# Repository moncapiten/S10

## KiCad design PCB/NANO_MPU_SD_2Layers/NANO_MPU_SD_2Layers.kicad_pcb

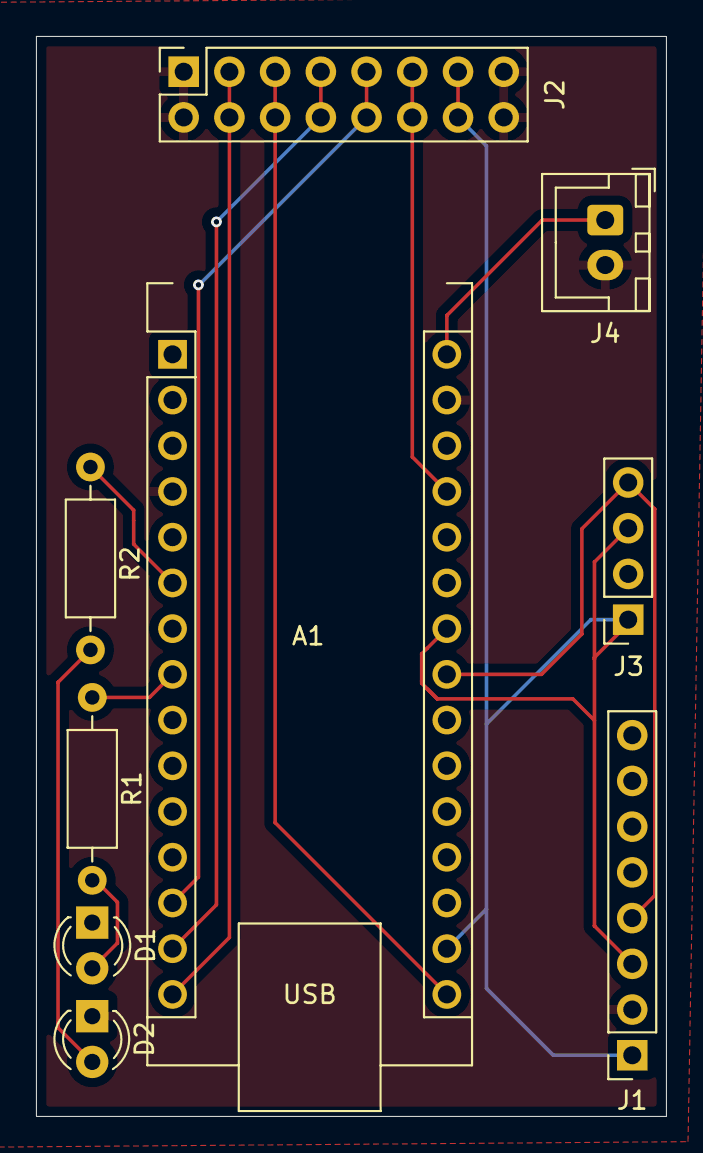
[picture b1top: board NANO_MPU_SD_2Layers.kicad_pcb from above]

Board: 2 copper layers, 35.0 x 60.0 mm, 9 parts (0 on the bottom side), 14 nets.

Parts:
A1: Arduino_Nano_v2.x; Arduino_Nano
D1, D2: LED; LED_D3.0mm_Clear
J1: Conn_01x08_Socket; PinSocket_1x08_P2.54mm_Vertical
J2: DIN41612_02x08_AB_EvenPins; PinSocket_2x08_P2.54mm_Vertical
J3: Conn_01x04_Socket; PinSocket_1x04_P2.54mm_Vertical
J4: Conn_01x02_Socket; JST_XH_B2B-XH-A_1x02_P2.50mm_Vertical
R1, R2: R; R_Axial_DIN0207_L6.3mm_D2.5mm_P10.16mm_Horizontal

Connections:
+3.3V: A1.17 (3V3), J1.1, J2.13 (Pin_b14), J2.14 (ePin_a14), J3.1
+5V: A1.27 (+5V), J2.11 (ePin_b12), J2.12 (ePin_a12)
GND: A1.4 (GND), A1.29 (GND), D1.1 (K), D2.1 (K), J1.2, J2.1 (ePin_b2), J2.2 (ePin_a2), J2.15 (ePin_b16), J2.16 (ePin_a16), J3.2, J4.2
unnamed: A1.23 (A4), J1.4, J3.4
unnamed: A1.24 (A5), J1.3, J3.3
unnamed: A1.6 (D3), R2.2
unnamed: A1.8 (D5), R1.1
unnamed: A1.13 (D10), J2.9 (ePin_b10), J2.10 (ePin_a10)
unnamed: A1.14 (D11), J2.7 (ePin_b8), J2.8 (ePin_a8)
unnamed: A1.15 (D12), J2.3 (eePin_b4), J2.4 (ePin_a4)
unnamed: A1.16 (D13), J2.5 (ePin_b6), J2.6 (ePin_a6)
unnamed: A1.30 (VIN), J4.1
unnamed: D1.2 (A), R1.2
unnamed: D2.2 (A), R2.1

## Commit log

2024-12-03 mhmhmhm
2024-12-03 made folders
2024-12-03 xmxmxmxmxm
2024-12-03 10sec Norris drivethrought
2024-12-03 DU DU DU DU
2024-12-03 CHE BORDELLO!
2024-12-03 added scan
2024-12-03 dunno added some stuff ig
2024-12-03 meaured data and made the code to measure the same data man
2024-12-03 added some data
2024-12-03 jajajaj
2024-12-09 not too sure tbh
2025-02-10 deseognFiles + data analysis
2025-02-11 done the stat anmalysis on all ASFs on all axis
2025-02-11 i draghi
2025-02-11 for now wrong values in ASF_stats but given correct by statAnal, gonna fix now
2025-02-11 calculated gs and now going to plot
2025-02-11 done measurement and plots
2025-02-11 done the graph
2025-02-11 new data dunmps
2025-02-12 trying to do temp analysis, will soon work on the other thing
2025-02-12 temperature analysis complete
2025-02-12 new data dump, lets see if its useful
2025-02-12 done the prientation recognizatin alg and working as intended
2025-02-12 redone media tree
2025-02-12 measured g data for statAnal in Pisa
2025-02-12 done data analysis on Pisa gathereed data and made plot
2025-02-12 ci siamo quasi
2025-02-12 done hists analysis
2025-02-12 stitichezza?
2025-02-12 changed a small lil thingi
2025-02-12 done apostrophes
2025-02-12 corrected the accelerometer and piezo stuff
2025-02-12 added a couple thingies to the pres
2025-02-12 added some pics
2025-02-12 done even more stuff
2025-02-12 added deltasigma stuff
2025-02-12 beauatify - M
2025-02-12 we did done de deed doy
2025-02-18 aggiunti dati sparsi
2025-02-18 roddi al pub
2025-02-19 final destination
